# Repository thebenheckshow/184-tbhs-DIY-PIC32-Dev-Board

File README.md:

# 184-tbhs-DIY-PIC32-Dev-Board

Published on May 8, 2015
Learn more about Molex connectors at - http://element14.com/molex

http://element14.com/tbhs - In this episode Ben builds his own PIC32 development board. Ben shows us how to design, assemble and test this custom solution. 

Like The Ben Heck Show at - http://facebook.com/benheckshow

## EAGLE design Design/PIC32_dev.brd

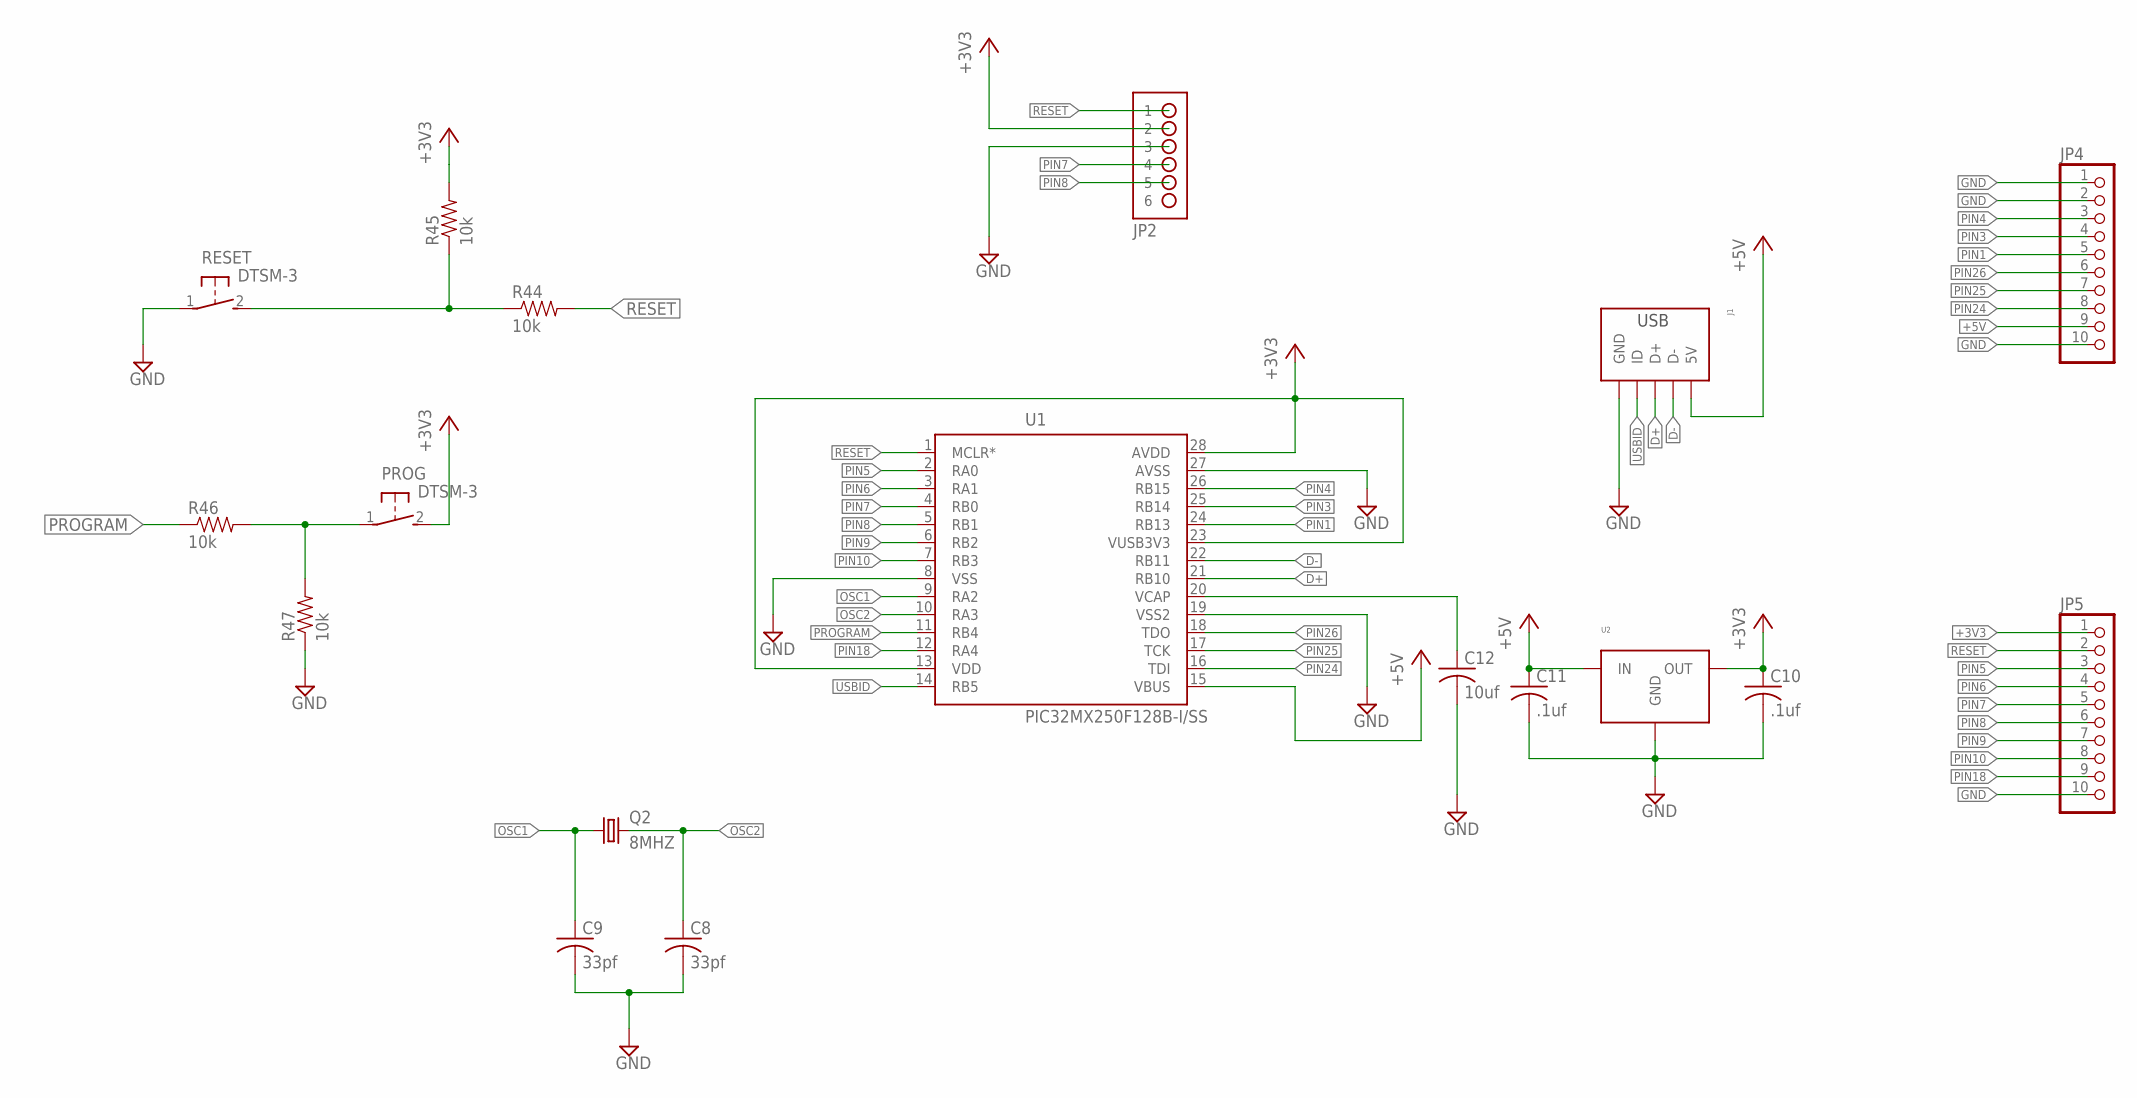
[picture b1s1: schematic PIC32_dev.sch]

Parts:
C8, C9: 33pf; C1206
C10, C11: .1uf; C1206
C12: 10uf; C1206
J1: USBMC32599; MC32599
JP2: HDR-1X6-OFFSET; HDR-1X6_OFFSET
JP4, JP5: PINHD-1X10; 1X10
PROG: DTSM-3
Q2: 8MHZ; CTS406
R44, R45, R46, R47: 10k; 1206
RESET: DTSM-3
U1: PIC32MX250F128B-I/SS; SOP65P780X200-28N
U2: FIXED_VOLTAGE_REGDPAK-3; DPAK-3

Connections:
+3V3: C10.1, JP2.2, JP5.1, PROG.2, R45.2, U1.13 (VDD), U1.23 (VUSB3V3), U1.28 (AVDD), U2.2 (OUT)
+5V: C11.1, J1.V_BUS (5V), JP4.9, U1.15 (VBUS), U2.1 (IN)
D+: J1.D+, U1.21 (RB10)
D-: J1.D-, U1.22 (RB11)
GND: C8.2, C9.2, C10.2, C11.2, C12.2, J1.GND, J1.SH_0 (GND), J1.SH_1 (GND), J1.SH_2 (GND), J1.SH_3 (GND), JP2.3, JP4.1, JP4.2, JP4.10, JP5.10, R47.1, RESET.1, U1.8 (VSS), U1.19 (VSS2), U1.27 (AVSS), U2.4 (GND)
unnamed: C12.1, U1.20 (VCAP)
unnamed: R44.1, R45.1, RESET.2
unnamed: PROG.1, R46.2, R47.2
OSC1: C9.1, Q2.1, U1.9 (RA2)
OSC2: C8.1, Q2.3 (2), U1.10 (RA3)
PIN1: JP4.5, U1.24 (RB13)
PIN3: JP4.4, U1.25 (RB14)
PIN4: JP4.3, U1.26 (RB15)
PIN5: JP5.3, U1.2 (RA0)
PIN6: JP5.4, U1.3 (RA1)
PIN7: JP2.4, JP5.5, U1.4 (RB0)
PIN8: JP2.5, JP5.6, U1.5 (RB1)
PIN9: JP5.7, U1.6 (RB2)
PIN10: JP5.8, U1.7 (RB3)
PIN18: JP5.9, U1.12 (RA4)
PIN24: JP4.8, U1.16 (TDI)
PIN25: JP4.7, U1.17 (TCK)
PIN26: JP4.6, U1.18 (TDO)
PROGRAM: R46.1, U1.11 (RB4)
RESET: JP2.1, JP5.2, R44.2, U1.1 (MCLR*)
USBID: J1.N/C (ID), U1.14 (RB5)

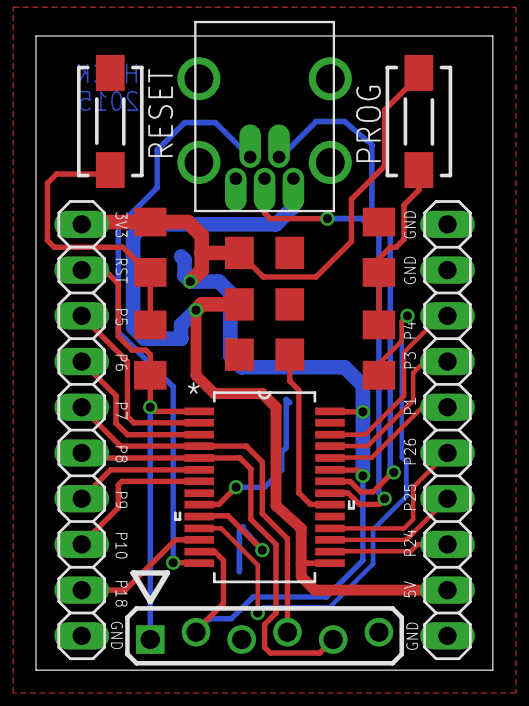
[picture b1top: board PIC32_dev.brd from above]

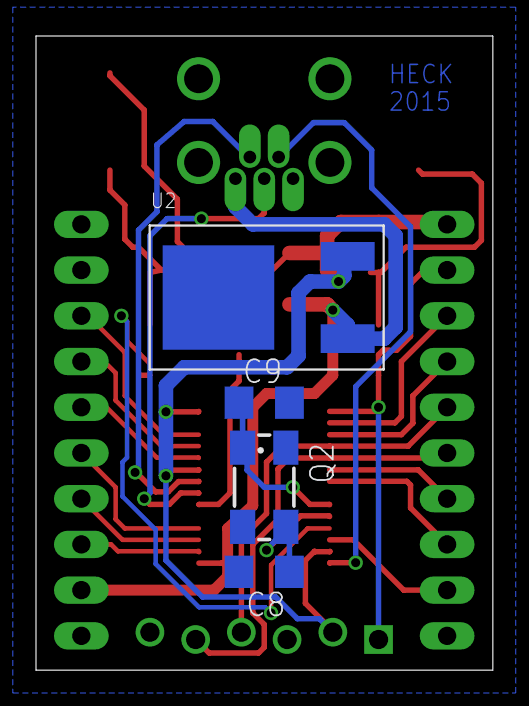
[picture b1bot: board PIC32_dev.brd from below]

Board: 2 copper layers, 25.4 x 35.2 mm, 18 parts (4 on the bottom side), 26 nets.

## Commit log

2016-12-06 Files are uploaded!

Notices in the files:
parts and their libraries:
SparkFun-Resistors: Licensing: CC v3.0 Share-Alike You are welcome to use this library for commercial purposes.
